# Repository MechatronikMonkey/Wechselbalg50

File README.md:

# Wechselbalg 50 (WB50)
Wechselbalg 50 is a 50‑watt tube guitar amplifier built entirely on a PCB. It combines classic British crunch with a modern high‑gain voice, switchable by relay. The name “Wechselbalg” (changeling) nods to the two distinct characters living in one chassis.

> Tagline (working): “Two voices, one heart of iron.”

## Highlights
- Two switchable voicings via relay (Classic ↔ Beast)
- Cascaded 12AX7 preamp with bright peakers
- Cathode follower into a classic T/M/B tone stack
 - Serial FX loop (always active; not bypassable); dual master volumes (post‑loop, RL3 selects)
- Long‑tail‑pair PI → 2× EL34 push‑pull power stage
- Classic British NFB with Presence & Thump (Resonance/Depth)
- Fixed, trimmable bias; regulated 12‑V rail (7812) for relays/loop
- Layout goals: star‑like grounding, short grid leads, disciplined heater routing, decoupled HT nodes

## Circuit overview
1) Input and V1: high‑value grid leak + grid stopper, cathode bypass options for British mid focus.  
2) Voicing section: relay switches additional gain/treble‑peaking networks for the Beast mode.  
3) Cathode follower → passive T/M/B tone stack for low‑impedance drive.  
4) FX loop: buffered send/return; always in circuit (no bypass); two post‑loop master volumes (Rhythm/Lead) with relay selection.  
5) Phase inverter: long‑tail‑pair (12AX7) with balanced plate loads.  
6) Power stage: 2× EL34 fixed‑bias push‑pull; screen resistors; coupling caps per side.  
7) Feedback shaping: Presence and Resonance inside the negative feedback leg from the output transformer secondary.  
8) Power supply: bridge rectifier, choke‑assisted filtering and stepped B+ distribution; regulated 12 V for control circuitry.

## Channel switching and controls
- Channel toggle (front) or footswitch (“SW.” jack) drives a common control line that actuates multiple relays:
	- RL1: preamp voicing (Plexi ↔ BE)
	- RL2: gain pot routing (Gain 1 ↔ Gain 2)
	- RL3: master selection (Volume 1 ↔ Volume 2, both post‑loop)
- The “SW.” jack is a latching footswitch input (no audio). With a plug inserted, the footswitch takes over; without it, the front‑panel CHANNEL mini‑toggle controls the state.
- Result: two distinct channels with their own Gain and Master settings while keeping the FX loop operating at a stable level.
 - Rear control: Thump (Resonance/Depth) shapes low‑frequency feedback for tighter vs. bigger low‑end feel.

## Safety
This project involves lethal voltages up to ~500 V. Only qualified persons should build or service it. Always discharge filter caps, use an isolation transformer, work one‑handed where possible, and wear eye protection.

## Scope & status
This repository aims at a reproducible PCB implementation of a classic small‑box‑style topology (without using protected brand names).  
Planned artifacts: schematic capture, PCB layout, BOM, bring‑up checklist and measurement notes.

## Naming
“Wechselbalg” = changeling/shapeshifter – a subtle hint at the two switchable voices. Short code: WB50.

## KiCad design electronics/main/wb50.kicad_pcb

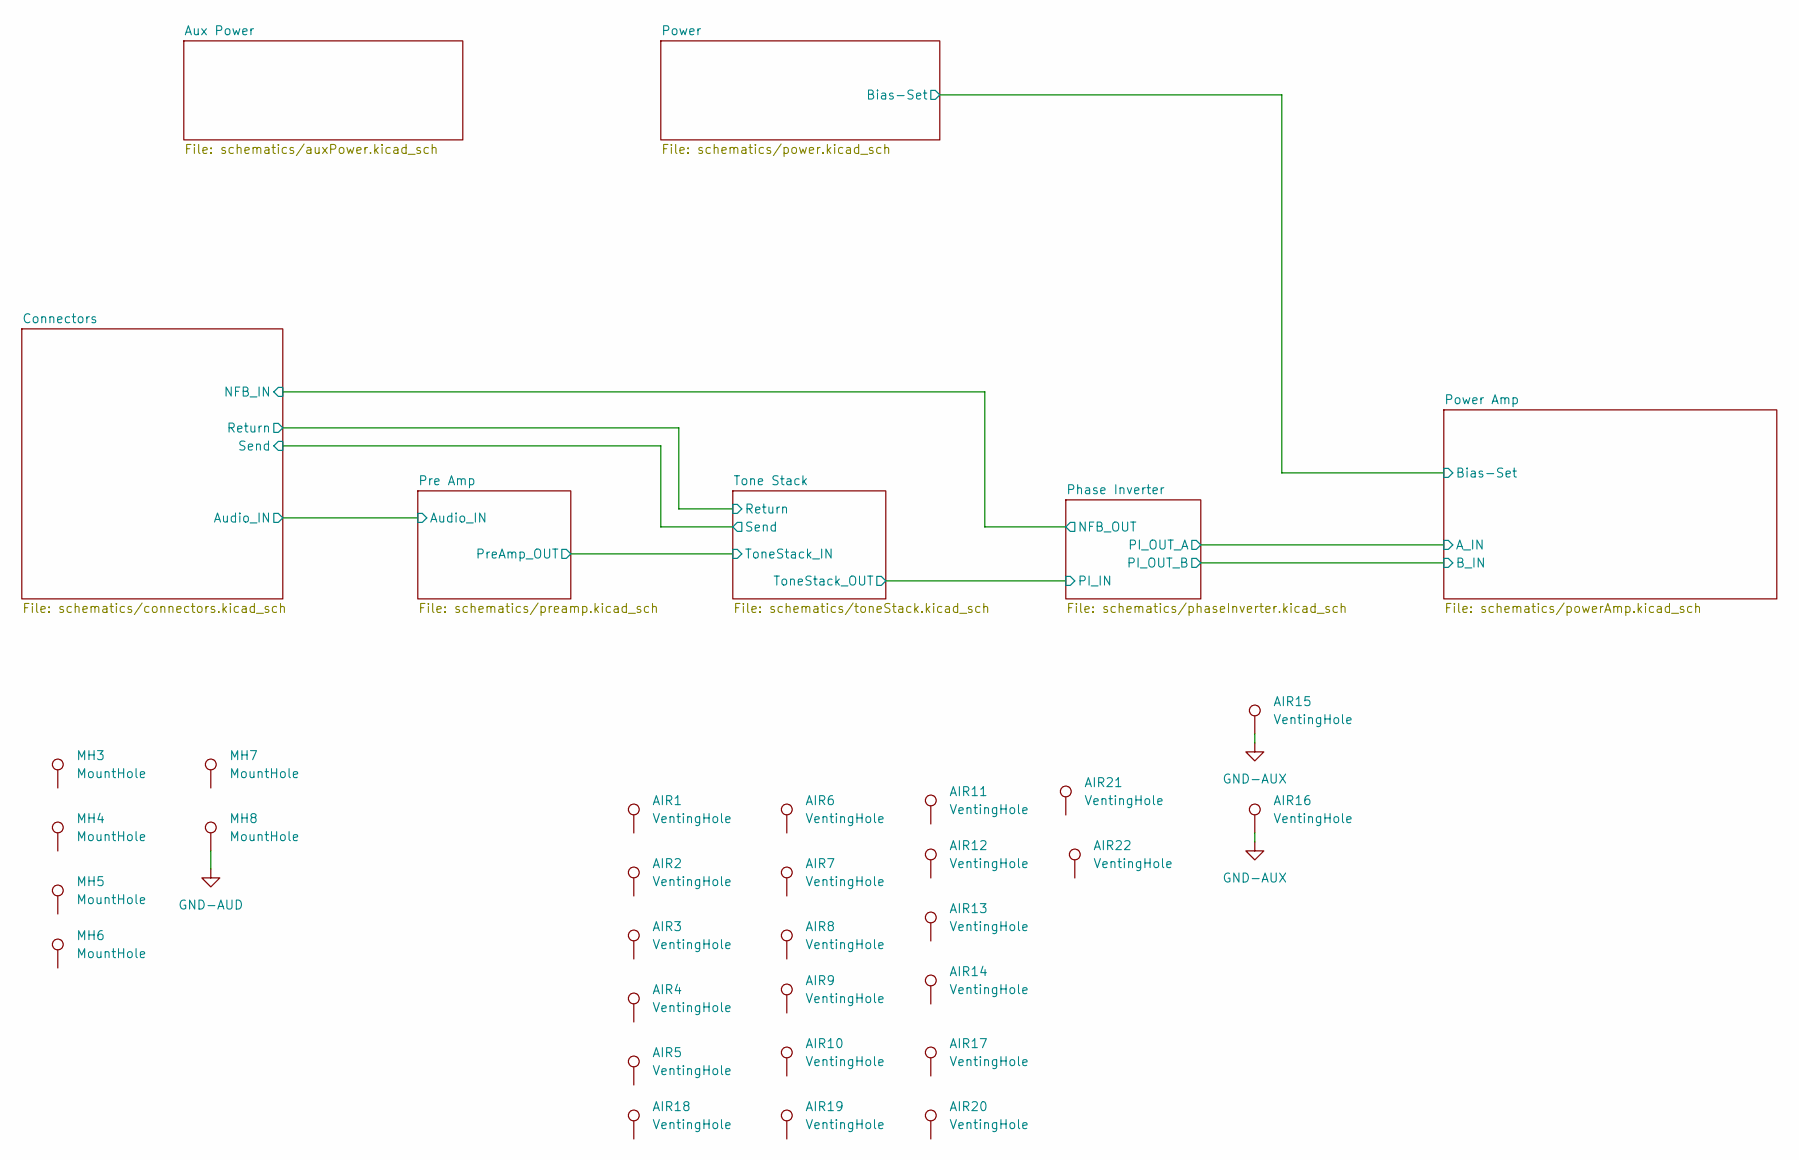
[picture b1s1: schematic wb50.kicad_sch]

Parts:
AIR1, AIR2, AIR3, AIR4, AIR5, AIR6, AIR7, AIR8, AIR9, AIR10, AIR11, AIR12, AIR13, AIR14, AIR15, AIR16, AIR17, AIR18, AIR19, AIR20, AIR21, AIR22: VentingHole; MountingHole_4.3mm_M4
MH3, MH4, MH5, MH6, MH7, MH8: MountHole; MountingHole_3.5mm_Pad_TopBottom

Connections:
GND-AUD: MH8.1; also elsewhere on the board

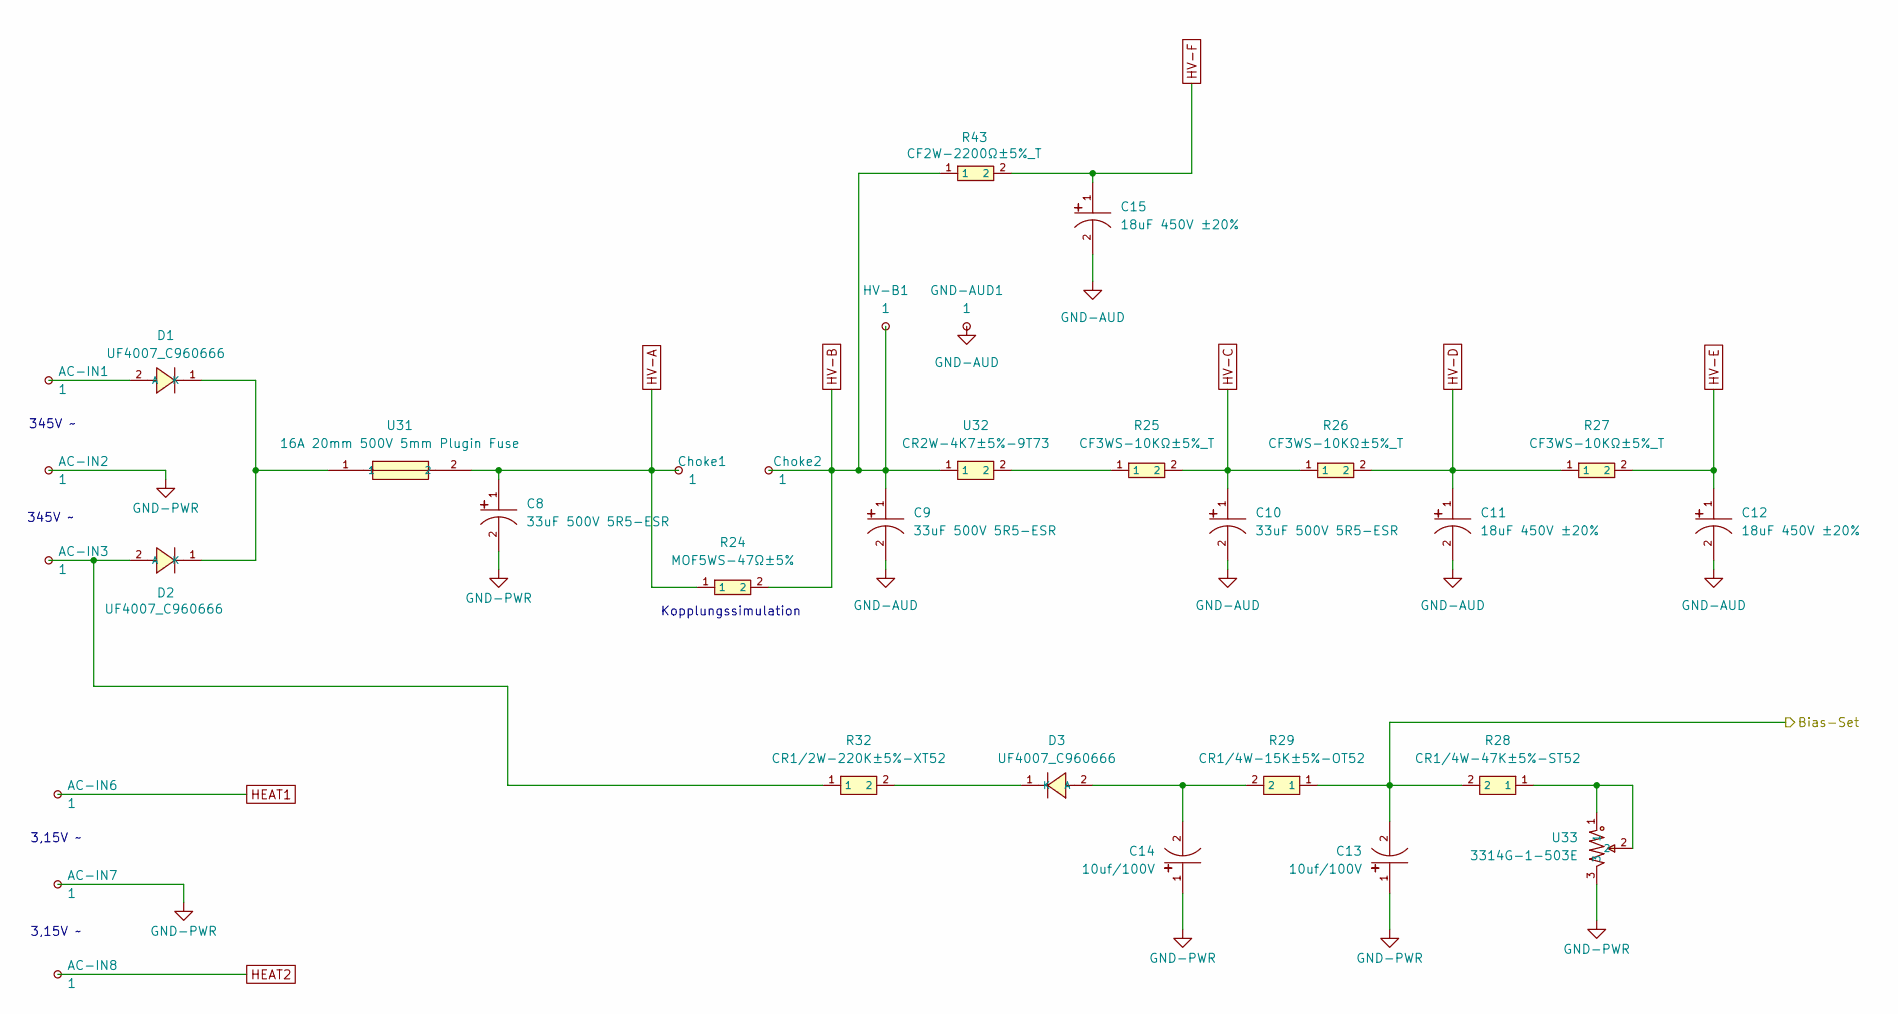
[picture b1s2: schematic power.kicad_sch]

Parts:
AC-IN1, AC-IN2, AC-IN3: 1; TestPoint_THTPad_D3.0mm_Drill1.5mm
AC-IN6, AC-IN7, AC-IN8: 1; TestPoint_THTPad_D4.0mm_Drill2.0mm
C8, C9, C10: 33uF 500V 5R5-ESR; CAP-TH_BD12.5-P5.00-D0.6-FD; LCSC C443401
C11, C12, C15: 18uF 450V ±20%; CAP-TH_BD10.0-P5.00-D1.0-FD; LCSC C781269
C13, C14: 10uf/100V; CAP-TH_BD6.3-P2.50-D1.0-FD; LCSC C2029
Choke1, Choke2: 1; TestPoint_THTPad_D2.5mm_Drill1.2mm
D1, D2, D3: UF4007_C960666; DO-41_BD2.4-L4.7-P8.70-D0.9-RD; LCSC C960666
GND-AUD1: 1; TestPoint_THTPad_D3.0mm_Drill1.5mm
HV-B1: 1; TestPoint_THTPad_D3.0mm_Drill1.5mm
R24: MOF5WS-47Ω±5%; RES-TH_BD6.0-L17.5-P21.50-D0.8; LCSC C121969
R25, R26, R27: CF3WS-10KΩ±5%_T; RES-TH_BD5.5-L15.0-P19.00-D0.8; LCSC C120810
R28: CR1/4W-47K±5%-ST52; RES-TH_BD2.7-L6.2-P10.20-D0.4; LCSC C2896823
R29: CR1/4W-15K±5%-OT52; RES-TH_BD2.7-L6.2-P10.20-D0.4; LCSC C2894565
R32: CR1/2W-220K±5%-XT52; RES-TH_BD3.5-L9.0-P13.00-D0.5; LCSC C2894491
R43: CF2W-2200Ω±5%_T; RES-TH_BD5.5-L15.0-P19.00-D0.8; LCSC C187501
U31: 16A 20mm 500V 5mm Plugin Fuse; FUSE-TH_L22.5-W10.8-P22.50_0031.8201.G; LCSC C3204125
U32: CR2W-4K7±5%-9T73; RES-TH_BD5.0-L15.5-P19.50-D0.7; LCSC C2903451
U33: 3314G-1-503E; RES-ADJ-SMD_3314G-1-103E; LCSC C719184

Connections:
/Power Amp/Bias-Set: C13.2, R28.2, R29.1; also elsewhere on the board
GND-AUD: C9.2, C10.2, C11.2, C12.2, C15.2, GND-AUD1.1; also elsewhere on the board
GND-PWR: AC-IN2.1, AC-IN7.1, C8.2, C13.1, C14.1, U33.3; also elsewhere on the board
HEAT1: AC-IN6.1; also elsewhere on the board
HEAT2: AC-IN8.1; also elsewhere on the board
HV-A: C8.1, Choke1.1, R24.1, U31.2; also elsewhere on the board
HV-B: C9.1, Choke2.1, HV-B1.1, R24.2, R43.1, U32.1; also elsewhere on the board
HV-C: C10.1, R25.2, R26.1; also elsewhere on the board
HV-D: C11.1, R26.2, R27.1; also elsewhere on the board
HV-E: C12.1, R27.2; also elsewhere on the board
HV-F: C15.1, R43.2; also elsewhere on the board
unnamed: AC-IN1.1, D1.2 (A)
unnamed: D1.1 (K), D2.1 (K), U31.1
unnamed: AC-IN3.1, D2.2 (A), R32.1
unnamed: C14.2, D3.2 (A), R29.2
unnamed: D3.1 (K), R32.2
unnamed: R25.1, U32.2
unnamed: R28.1, U33.1, U33.2

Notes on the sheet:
345V ~
3,15V ~
Kopplungssimulation

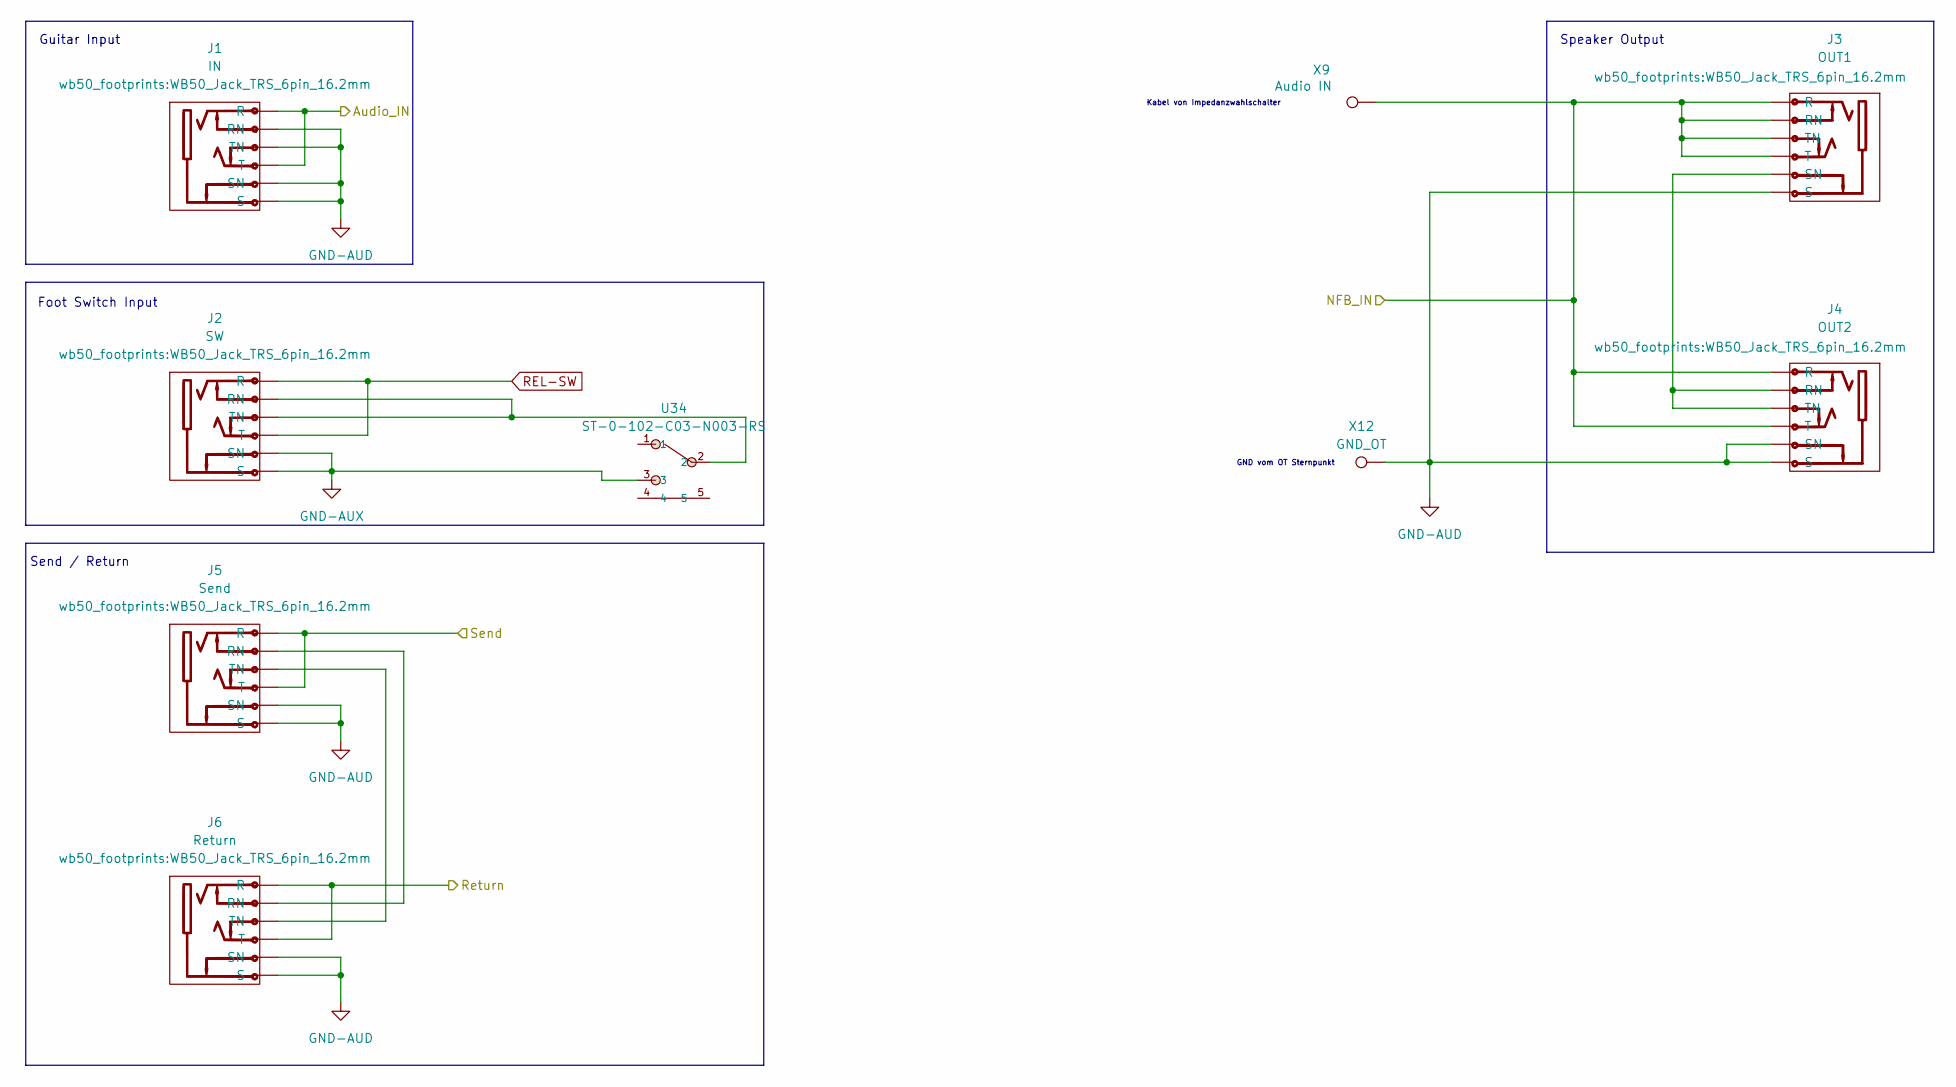
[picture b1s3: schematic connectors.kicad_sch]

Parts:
J1: IN; WB50_Jack_TRS_6pin_16.2mm
J2: SW; WB50_Jack_TRS_6pin_16.2mm
J3: OUT1; WB50_Jack_TRS_6pin_16.2mm
J4: OUT2; WB50_Jack_TRS_6pin_16.2mm
J5: Send; WB50_Jack_TRS_6pin_16.2mm
J6: Return; WB50_Jack_TRS_6pin_16.2mm
U34: ST-0-102-C03-N003-RS; SW-TH_ST-0-102-C03-N003-RS; LCSC C1788489
X9: Audio IN; TestPoint_THTPad_D4.0mm_Drill2.0mm
X12: GND_OT; TestPoint_THTPad_D4.0mm_Drill2.0mm

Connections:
/Connectors/Audio_IN: J1.2 (R), J1.3 (T); also elsewhere on the board
/Connectors/NFB_IN: J3.2 (R), J3.3 (T), J3.4 (TN), J3.5 (RN), J4.2 (R), J4.3 (T), X9.1; also elsewhere on the board
/Connectors/Return: J6.2 (R), J6.3 (T); also elsewhere on the board
/Connectors/Send: J5.2 (R), J5.3 (T); also elsewhere on the board
GND-AUD: J1.1 (S), J1.4 (TN), J1.5 (RN), J1.6 (SN), J3.1 (S), J4.1 (S), J4.6 (SN), J5.1 (S), J5.6 (SN), J6.1 (S), J6.6 (SN), X12.1; also elsewhere on the board
GND-AUX: J2.1 (S), J2.6 (SN), U34.3; also elsewhere on the board
unnamed: J2.4 (TN), J2.5 (RN), U34.2
unnamed: J3.6 (SN), J4.4 (TN), J4.5 (RN)
unnamed: J5.5 (RN), J6.5 (RN)
unnamed: J5.4 (TN), J6.4 (TN)
REL-SW: J2.2 (R), J2.3 (T); also elsewhere on the board

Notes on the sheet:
Foot Switch Input
Kabel von Impedanzwahlschalter
GND vom OT Sternpunkt
Guitar Input
Send / Return
Speaker Output

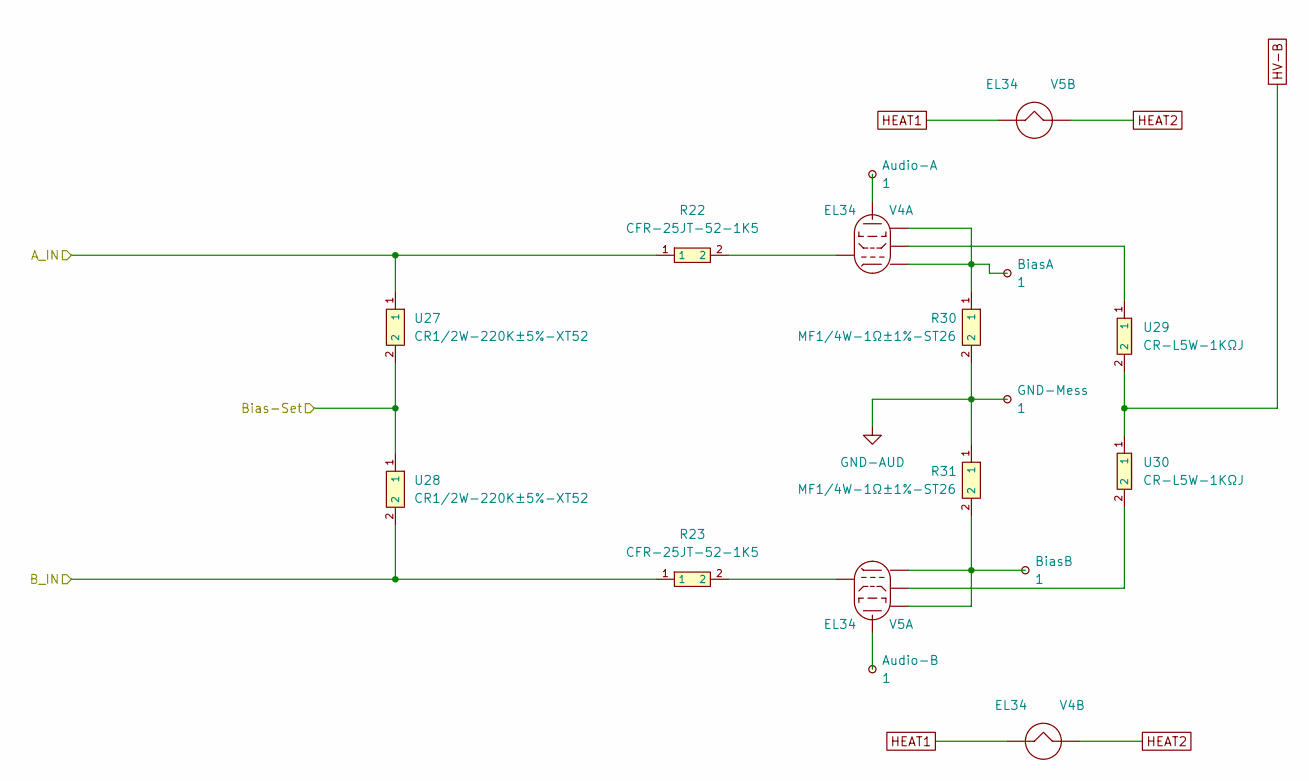
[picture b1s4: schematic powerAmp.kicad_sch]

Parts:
Audio-A: 1; TestPoint_THTPad_D3.0mm_Drill1.5mm
Audio-B: 1; TestPoint_THTPad_D3.0mm_Drill1.5mm
BiasA: 1; TestPoint_Pad_D2.0mm
BiasB: 1; TestPoint_Pad_D2.0mm
GND-Mess: 1; TestPoint_Pad_D2.0mm
R22, R23: CFR-25JT-52-1K5; RES-TH_BD2.4-L6.3-P10.30-D0.6; LCSC C1370569
R30, R31: MF1/4W-1Ω±1%-ST26; RES-TH_BD2.7-L6.2-P10.20-D0.4; LCSC C2903254
U27, U28: CR1/2W-220K±5%-XT52; RES-TH_BD3.5-L9.0-P13.00-D0.5; LCSC C2894491
U29, U30: CR-L5W-1KΩJ; RES-TH_BD9.5-L22.0-P26.00-D0.7; LCSC C334294
V4, V5: EL34; WB50_Socket_Octal_8Pin_D26.0mm_Hole2.0mm

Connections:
/Phase Inverter/PI_OUT_A: R22.1, U27.1; also elsewhere on the board
/Phase Inverter/PI_OUT_B: R23.1, U28.2; also elsewhere on the board
/Power Amp/Bias-Set: U27.2, U28.1; also elsewhere on the board
GND-AUD: GND-Mess.1, R30.2, R31.1; also elsewhere on the board
HEAT1: V4.2 (f), V5.2 (f); also elsewhere on the board
HEAT2: V4.7 (f), V5.7 (f); also elsewhere on the board
HV-B: U29.2, U30.1; also elsewhere on the board
unnamed 82: Audio-A.1, V4.3 (a); also elsewhere on the board
unnamed: R22.2, V4.5 (g1)
unnamed: U29.1, V4.4 (g2)
unnamed 85: BiasA.1, R30.1, V4.1 (g3), V4.8 (k); also elsewhere on the board
unnamed 86: Audio-B.1, V5.3 (a); also elsewhere on the board
unnamed: R23.2, V5.5 (g1)
unnamed: U30.2, V5.4 (g2)
unnamed 89: BiasB.1, R31.2, V5.1 (g3), V5.8 (k); also elsewhere on the board

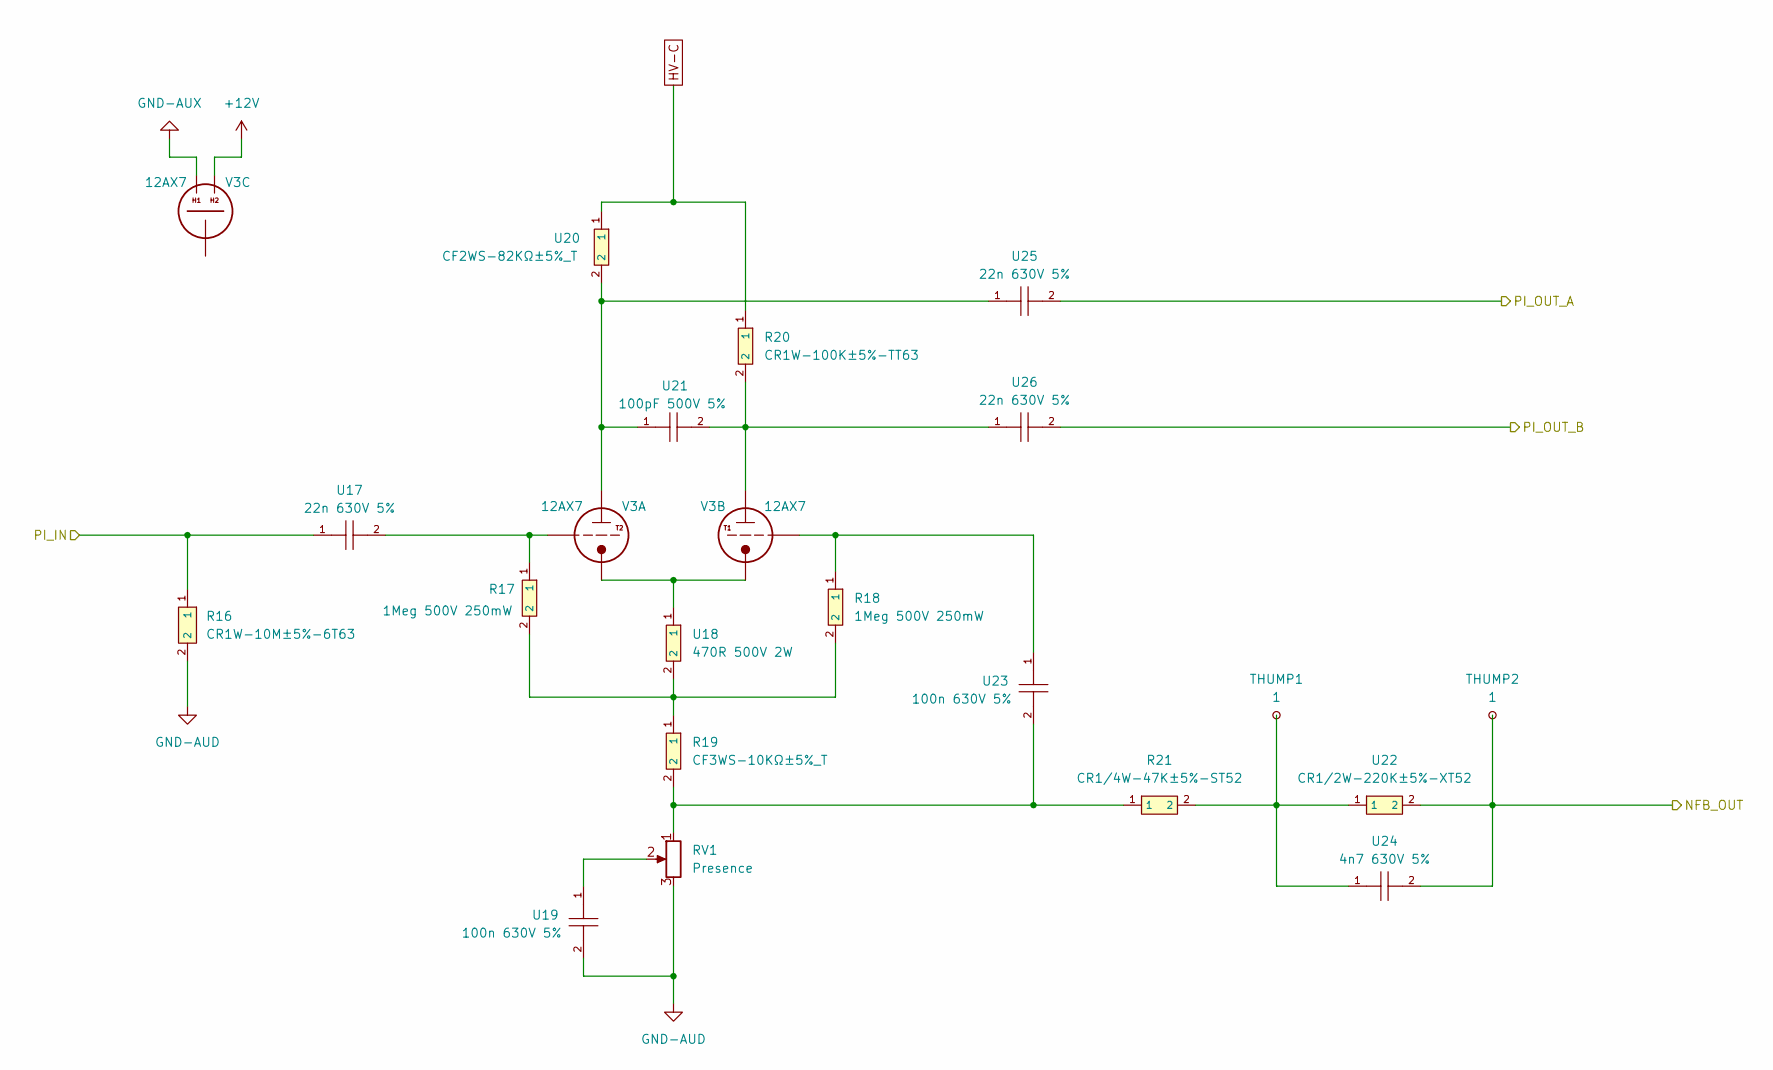
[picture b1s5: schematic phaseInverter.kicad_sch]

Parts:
R16: CR1W-10M±5%-6T63; RES-TH_BD4.5-L11.0-P15.00-D0.7; LCSC C2897121
R17, R18: 1Meg 500V 250mW; RES-TH_BD2.4-L6.3-P10.30-D0.6; LCSC C1370556
R19: CF3WS-10KΩ±5%_T; RES-TH_BD5.5-L15.0-P19.00-D0.8; LCSC C120810
R20: CR1W-100K±5%-TT63; RES-TH_BD4.5-L11.0-P15.00-D0.7; LCSC C601829
R21: CR1/4W-47K±5%-ST52; RES-TH_BD2.7-L6.2-P10.20-D0.4; LCSC C2896823
RV1: Presence; WB50_Pot_Omeg_PC20BU_P5.00mm
THUMP1, THUMP2: 1; TestPoint_THTPad_D2.0mm_Drill1.0mm
U17, U25, U26: 22n 630V 5%; MUSTARD_CAP_D8.5_L20.5_P25.5
U18: 470R 500V 2W; RES-TH_BD5.0-L15.5-P19.50-D0.7; LCSC C2905226
U19, U23: 100n 630V 5%; MUSTARD_CAP_D10_L32_P40.4
U20: CF2WS-82KΩ±5%_T; RES-TH_BD4.0-L11.5-P15.50-D0.7; LCSC C120647
U21: 100pF 500V 5%; MICA_CAP_L15.5_W3.6_P8.7
U22: CR1/2W-220K±5%-XT52; RES-TH_BD3.5-L9.0-P13.00-D0.5; LCSC C2894491
U24: 4n7 630V 5%; MUSTARD_CAP_D8.5_L20.5_P25.5
V3: 12AX7; WB50_Socket_Noval_9Pin_D21.0mm_Hole1.8mm

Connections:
+12V: V3.4 (H1); also elsewhere on the board
/Connectors/NFB_IN: THUMP2.1, U22.2, U24.2; also elsewhere on the board
/Phase Inverter/PI_IN: R16.1, U17.1; also elsewhere on the board
/Phase Inverter/PI_OUT_A: U25.2; also elsewhere on the board
/Phase Inverter/PI_OUT_B: U26.2; also elsewhere on the board
GND-AUD: R16.2, RV1.3, U19.2; also elsewhere on the board
GND-AUX: V3.5 (H2); also elsewhere on the board
HV-C: R20.1, U20.1; also elsewhere on the board
unnamed: R17.2, R18.2, R19.1, U18.2
unnamed: R19.2, R21.1, RV1.1, U23.2
unnamed: R21.2, THUMP1.1, U22.1, U24.1
unnamed: RV1.2, U19.1
unnamed: U20.2, U21.1, U25.1, V3.1 (A/P)
unnamed: U18.1, V3.3 (C/K), V3.8 (C/K)
unnamed: R17.1, U17.2, V3.2 (G)
unnamed: R20.2, U21.2, U26.1, V3.6 (A/P)
unnamed: R18.1, U23.1, V3.7 (G)

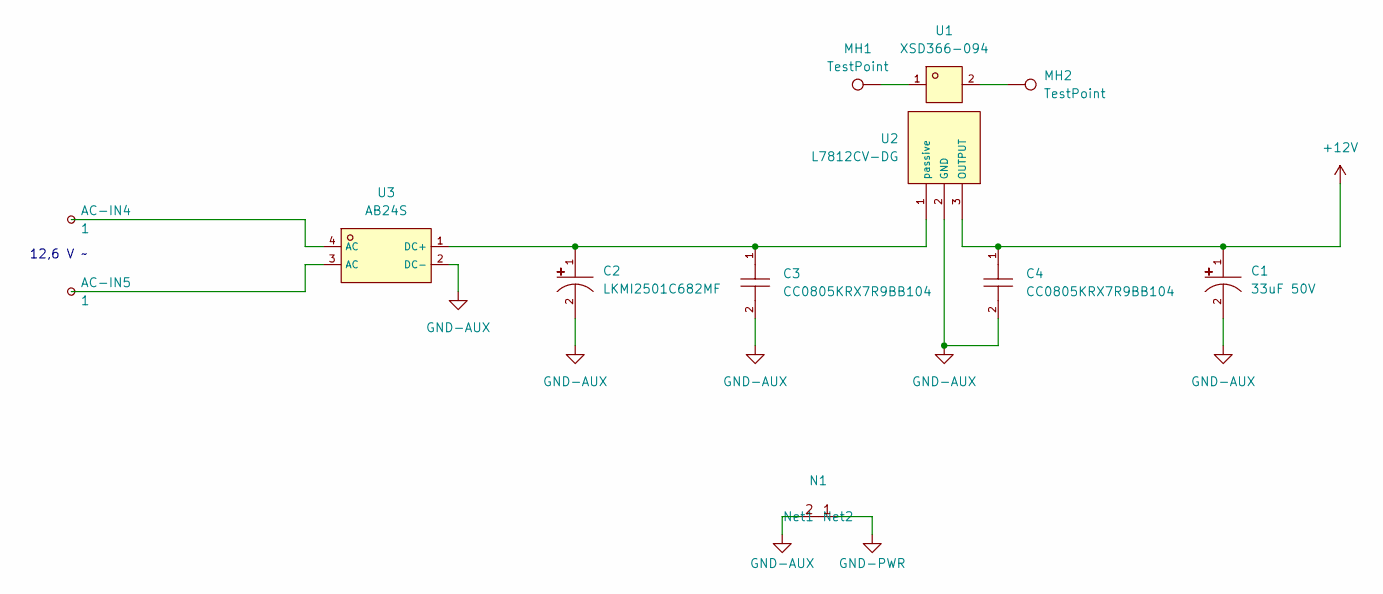
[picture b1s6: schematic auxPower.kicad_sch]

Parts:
AC-IN4, AC-IN5: 1; TestPoint_THTPad_D3.0mm_Drill1.5mm
C1: 33uF 50V; CAP-TH_BD5.0-P2.00-D0.8-FD; LCSC C89792
C2: LKMI2501C682MF; CAP-TH_BD16.0-P7.50-D1.2-FD; LCSC C442803
C3, C4: CC0805KRX7R9BB104; C0805; LCSC C49678
MH1, MH2: TestPoint; MountingHole_2.2mm_M2_DIN965_Pad_TopBottom
N1: NetTie_0.5mm_2Pad
U1: XSD366-094; HEATSINK-TH_XSD366-094; LCSC C286227
U2: L7812CV-DG; TO-220-3_L10.0-W4.5-P2.54-L; LCSC C2914
U3: AB24S; ABS-SMD_L5.0-W4.4-P4.00-LS7.0-BL; LCSC C882375

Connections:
+12V: C1.1, C4.1, U2.3 (OUTPUT); also elsewhere on the board
GND-AUX: C1.2, C2.2, C3.2, C4.2, N1.2 (Net2), U2.2 (GND), U3.2 (DC-); also elsewhere on the board
GND-PWR: N1.1 (Net1); also elsewhere on the board
unnamed: AC-IN4.1, U3.4 (AC)
unnamed: AC-IN5.1, U3.3 (AC)
unnamed: MH1.1, U1.1
unnamed: MH2.1, U1.2
unnamed: C2.1, C3.1, U2.1 (passive), U3.1 (DC+)

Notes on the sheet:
12,6 V ~

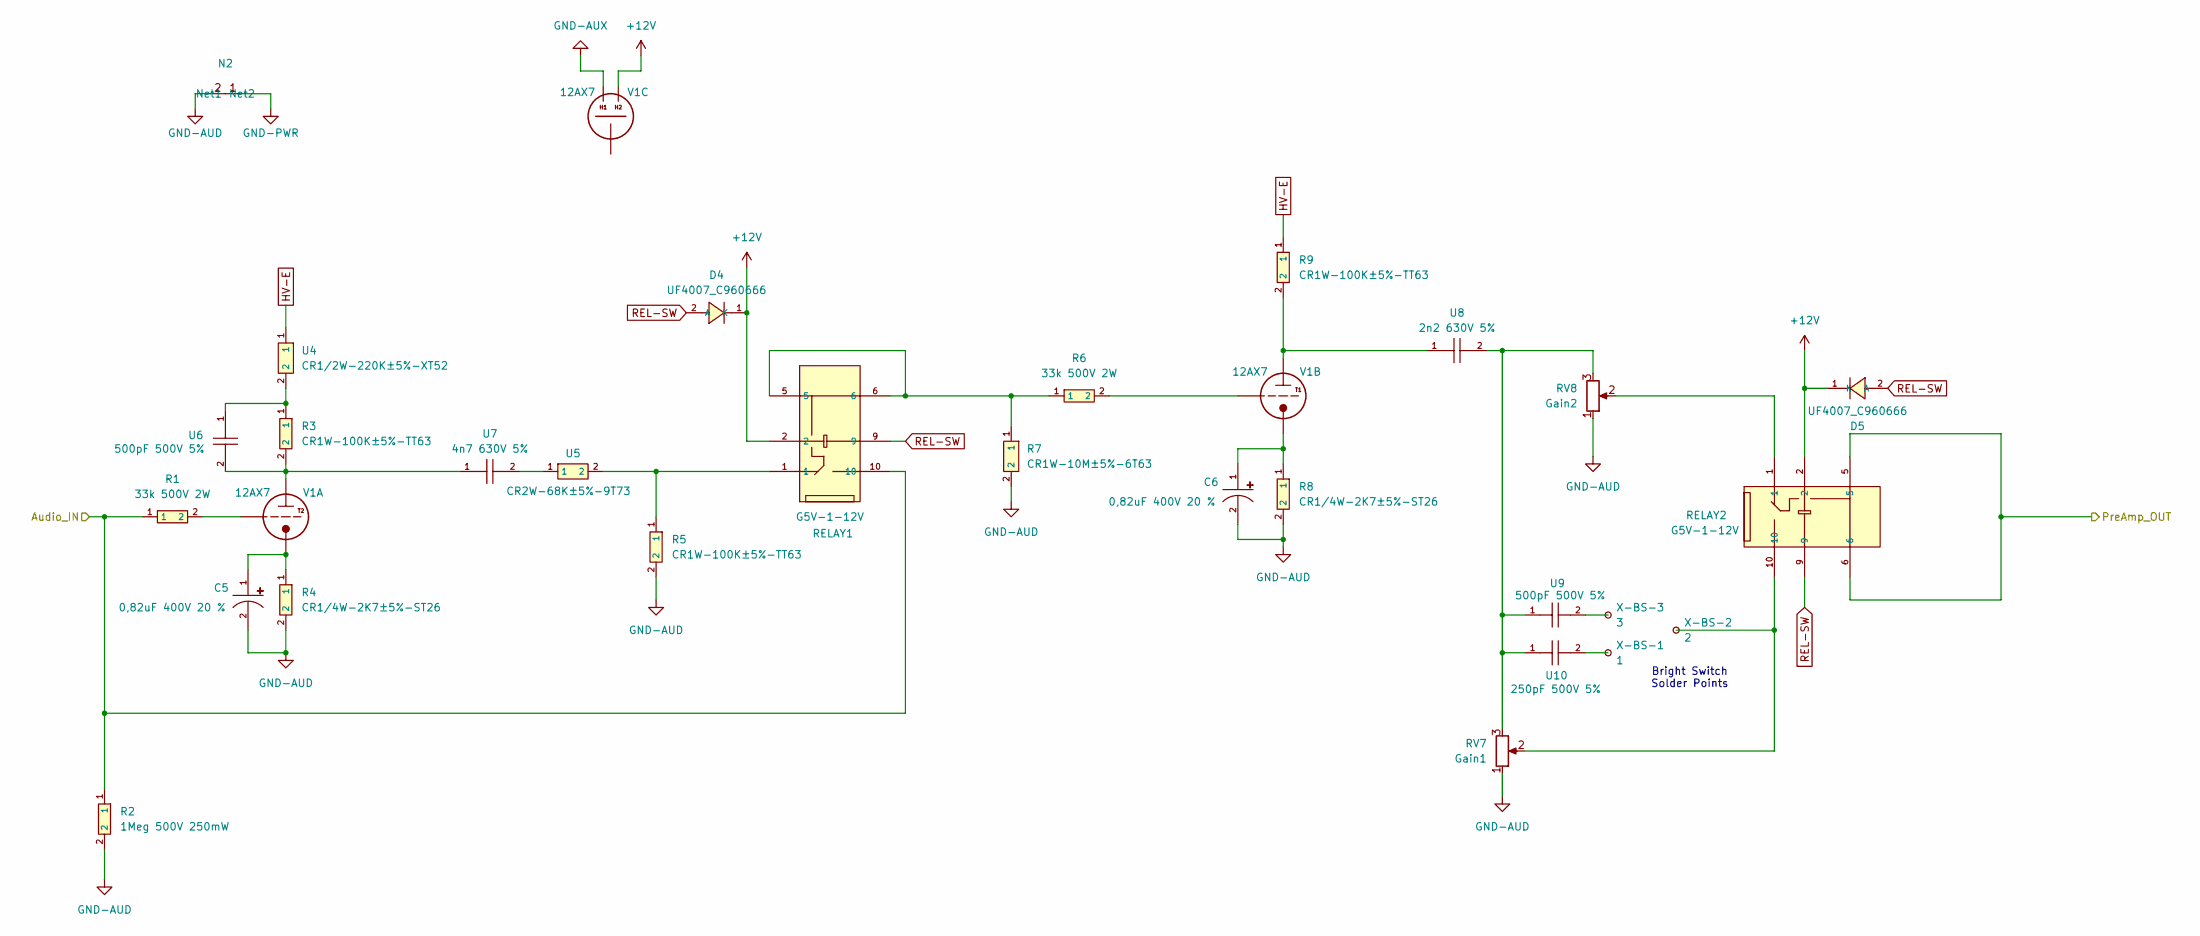
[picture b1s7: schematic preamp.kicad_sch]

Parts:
C5, C6: 0,82uF 400V 20 %; CAP-TH_BD6.3-P2.50-D1.0-FD; LCSC C2029
D4, D5: UF4007_C960666; DO-41_BD2.4-L4.7-P8.70-D0.9-RD; LCSC C960666
N2: NetTie_0.5mm_2Pad
R1, R6: 33k 500V 2W; RES-TH_BD3.0-L9.5-P13.50-D0.6; LCSC C70845
R2: 1Meg 500V 250mW; RES-TH_BD2.4-L6.3-P10.30-D0.6; LCSC C1370556
R3, R5, R9: CR1W-100K±5%-TT63; RES-TH_BD4.5-L11.0-P15.00-D0.7; LCSC C601829
R4, R8: CR1/4W-2K7±5%-ST26; RES-TH_BD2.7-L6.2-P10.20-D0.4; LCSC C2894624
R7: CR1W-10M±5%-6T63; RES-TH_BD4.5-L11.0-P15.00-D0.7; LCSC C2897121
RELAY1, RELAY2: G5V-1-12V; RELAY-TH_G5V-1; LCSC C31113
RV7: Gain1; WB50_Pot_Omeg_PC20BU_P5.00mm
RV8: Gain2; WB50_Pot_Omeg_PC20BU_P5.00mm
U4: CR1/2W-220K±5%-XT52; RES-TH_BD3.5-L9.0-P13.00-D0.5; LCSC C2894491
U5: CR2W-68K±5%-9T73; RES-TH_BD5.0-L15.5-P19.50-D0.7; LCSC C2903458
U6, U9: 500pF 500V 5%; MICA_CAP_L15.5_W3.6_P8.7
U7: 4n7 630V 5%; MUSTARD_CAP_D8.5_L20.5_P25.5
U8: 2n2 630V 5%; MUSTARD_CAP_D8.5_L20.5_P25.5
U10: 250pF 500V 5%; MICA_CAP_L15.5_W3.6_P8.7
V1: 12AX7; WB50_Socket_Noval_9Pin_D21.0mm_Hole1.8mm
X-BS-1: 1; TestPoint_THTPad_D3.0mm_Drill1.5mm
X-BS-2: 2; TestPoint_THTPad_D3.0mm_Drill1.5mm
X-BS-3: 3; TestPoint_THTPad_D3.0mm_Drill1.5mm

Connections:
+12V: D4.1 (K), D5.1 (K), RELAY1.2, RELAY2.2, V1.4 (H1); also elsewhere on the board
/Connectors/Audio_IN: R1.1, R2.1, RELAY1.10; also elsewhere on the board
/Pre Amp/PreAmp_OUT: RELAY2.5, RELAY2.6; also elsewhere on the board
GND-AUD: C5.2, C6.2, N2.2 (Net2), R2.2, R4.2, R5.2, R7.2, R8.2, RV7.1, RV8.1; also elsewhere on the board
GND-AUX: V1.5 (H2); also elsewhere on the board
GND-PWR: N2.1 (Net1); also elsewhere on the board
HV-E: R9.1, U4.1; also elsewhere on the board
unnamed: R3.1, U4.2, U6.1
unnamed: R5.1, RELAY1.1, U5.2
unnamed: R6.1, R7.1, RELAY1.5, RELAY1.6
unnamed: RELAY2.1, RV8.2
unnamed 52: RELAY2.10, RV7.2, X-BS-2.1; also elsewhere on the board
unnamed: RV7.3, RV8.3, U8.2, U9.1, U10.1
unnamed: U5.1, U7.2
unnamed 65: U10.2, X-BS-1.1; also elsewhere on the board
unnamed 66: U9.2, X-BS-3.1; also elsewhere on the board
unnamed: R3.2, U6.2, U7.1, V1.1 (A/P)
unnamed: C5.1, R4.1, V1.3 (C/K)
unnamed: R1.2, V1.2 (G)
unnamed: R9.2, U8.1, V1.6 (A/P)
unnamed: C6.1, R8.1, V1.8 (C/K)
unnamed: R6.2, V1.7 (G)
REL-SW: D4.2 (A), D5.2 (A), RELAY1.9, RELAY2.9; also elsewhere on the board

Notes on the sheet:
Bright Switch Solder Points
